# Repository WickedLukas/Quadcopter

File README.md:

# Quadcopter
Teensy 3.6 Quadcopter

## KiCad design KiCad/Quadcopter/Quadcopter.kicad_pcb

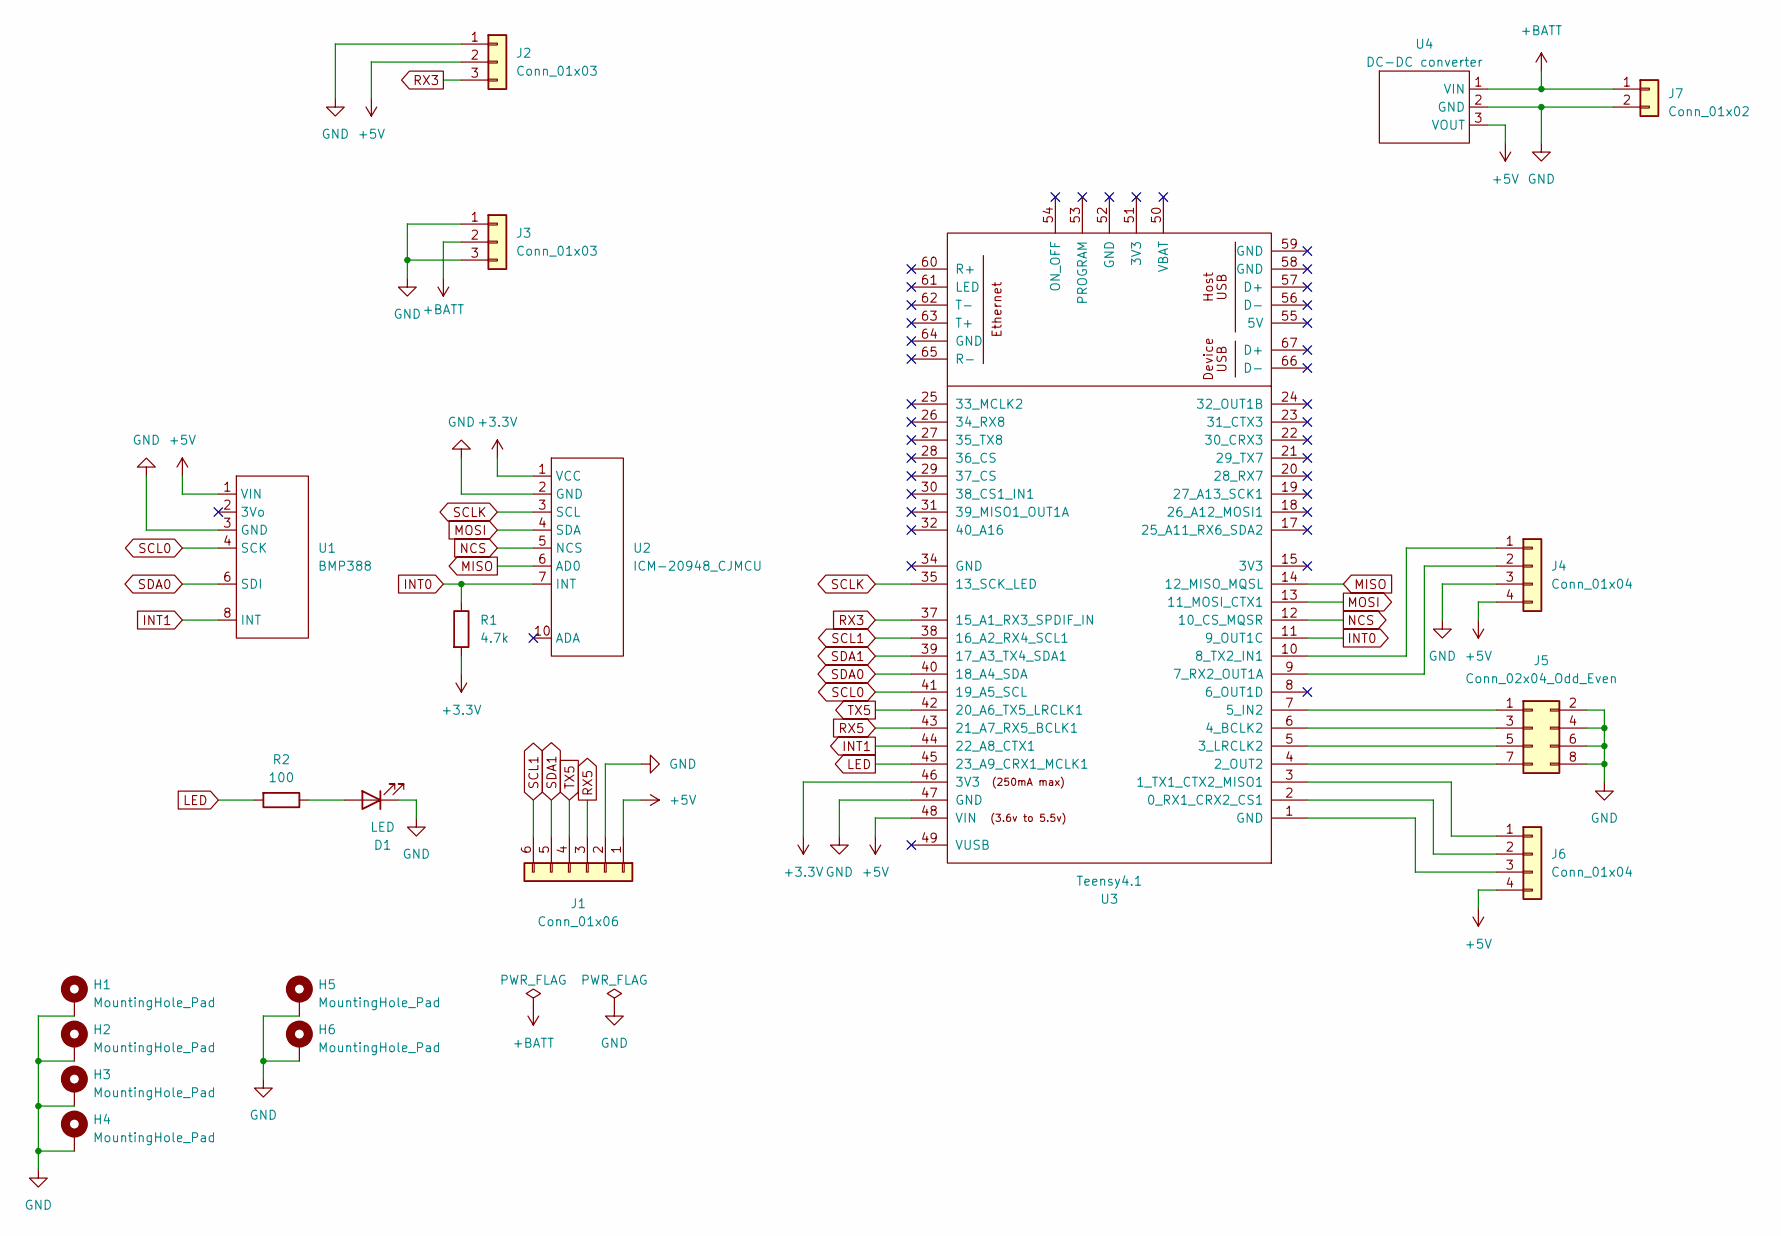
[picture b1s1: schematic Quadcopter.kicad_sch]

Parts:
D1: LED; LED_D5.0mm
H1, H2, H3, H4, H5, H6: MountingHole_Pad; MountingHole_3.2mm_M3_Pad
J1: Conn_01x06; PinHeader_1x06_P2.54mm_Horizontal
J2, J3: Conn_01x03; PinHeader_1x03_P2.54mm_Horizontal
J4, J6: Conn_01x04; PinHeader_1x04_P2.54mm_Horizontal
J5: Conn_02x04_Odd_Even; PinHeader_2x04_P2.54mm_Horizontal
J7: Conn_01x02; 691402910002B
R1: 4.7k; R_Axial_DIN0207_L6.3mm_D2.5mm_P7.62mm_Horizontal
R2: 100; R_Axial_DIN0207_L6.3mm_D2.5mm_P7.62mm_Horizontal
U1: BMP388
U2: ICM-20948_CJMCU
U3: Teensy4.1; Teensy41
U4: DC-DC converter

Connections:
+3.3V: R1.2, U2.1 (VCC), U3.46 (3V3)
+5V: J1.1, J2.2, J4.4, J6.4, U1.1 (VIN), U3.48 (VIN), U4.3 (VOUT)
+BATT: J3.2, J7.1, U4.1 (VIN)
GND: D1.1 (K), H1.1, H2.1, H3.1, H4.1, H5.1, H6.1, J1.2, J2.1, J3.1, J3.3, J4.3, J5.2, J5.4, J5.6, J5.8, J7.2, U1.3 (GND), U2.2 (GND), U3.47 (GND), U4.2 (GND)
INT0: R1.1, U2.7 (INT), U3.11 (9_OUT1C)
INT1: U1.8 (INT), U3.44 (22_A8_CTX1)
LED: R2.2, U3.45 (23_A9_CRX1_MCLK1)
MISO: U2.6 (AD0), U3.14 (12_MISO_MQSL)
MOSI: U2.4 (SDA), U3.13 (11_MOSI_CTX1)
NCS: U2.5 (NCS), U3.12 (10_CS_MQSR)
unnamed: D1.2 (A), R2.1
unnamed: J4.1, U3.10 (8_TX2_IN1)
unnamed: J4.2, U3.9 (7_RX2_OUT1A)
unnamed: J5.1, U3.7 (5_IN2)
unnamed: J5.3, U3.6 (4_BCLK2)
unnamed: J5.5, U3.5 (3_LRCLK2)
unnamed: J5.7, U3.4 (2_OUT2)
unnamed: J6.1, U3.3 (1_TX1_CTX2_MISO1)
unnamed: J6.2, U3.2 (0_RX1_CRX2_CS1)
unnamed: J6.3, U3.1 (GND)
RX3: J2.3, U3.37 (15_A1_RX3_SPDIF_IN)
RX5: J1.3, U3.43 (21_A7_RX5_BCLK1)
SCL0: U1.4 (SCK), U3.41 (19_A5_SCL)
SCL1: J1.6, U3.38 (16_A2_RX4_SCL1)
SCLK: U2.3 (SCL), U3.35 (13_SCK_LED)
SDA0: U1.6 (SDI), U3.40 (18_A4_SDA)
SDA1: J1.5, U3.39 (17_A3_TX4_SDA1)
TX5: J1.4, U3.42 (20_A6_TX5_LRCLK1)

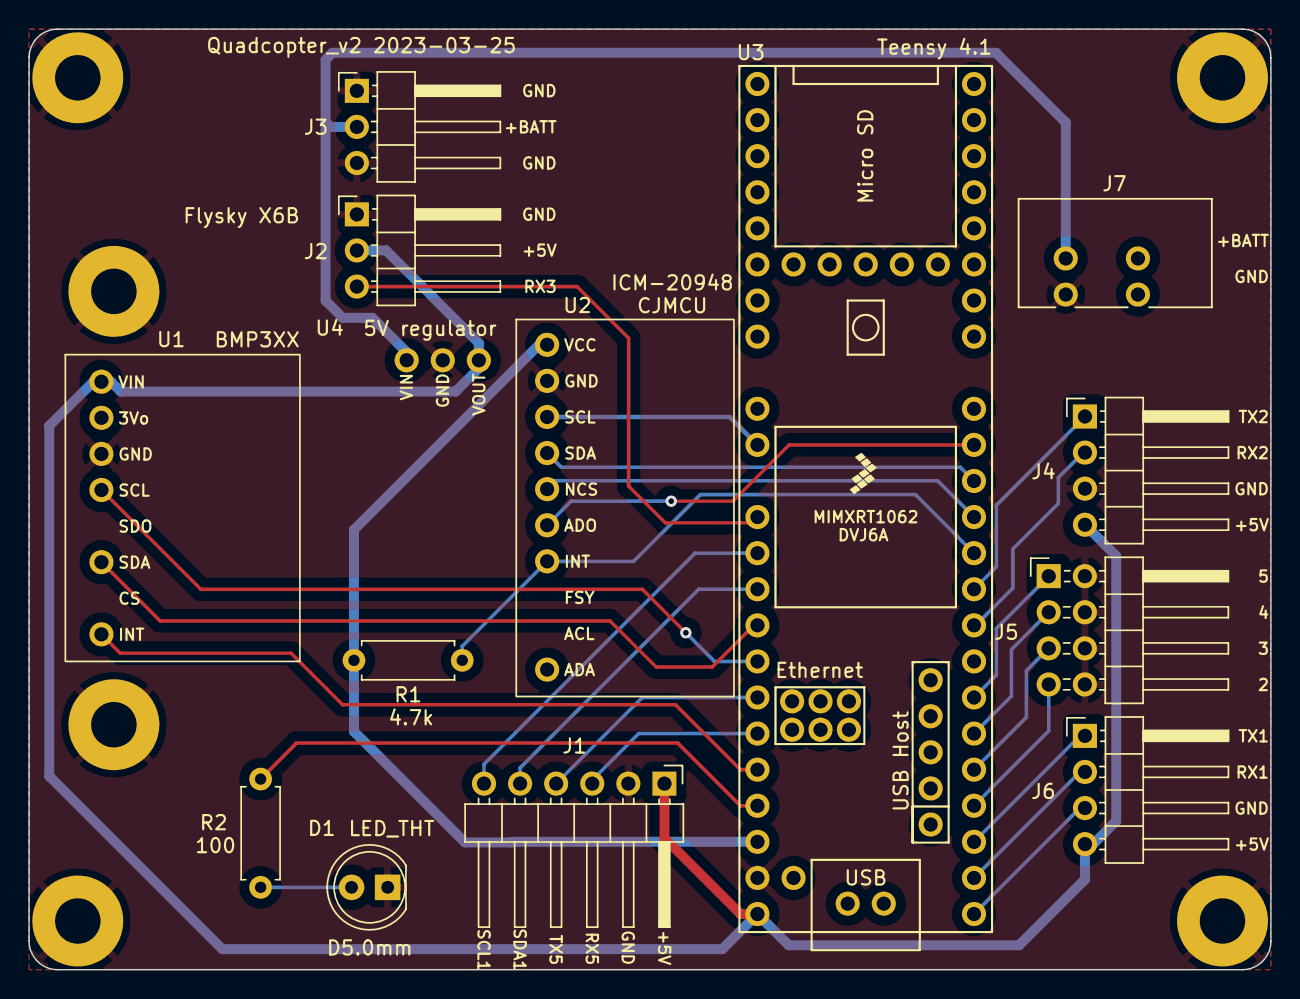
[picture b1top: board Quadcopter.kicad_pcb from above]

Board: 2 copper layers, 87.4 x 66.2 mm, 20 parts (0 on the bottom side), 28 nets.

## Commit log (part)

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2019-04-27 Initial commit which integrates a library for the Invensense ICM-20948 IMU.
    The Invensense ICM-20948 library was created by David Törnqvist and is based on the Invensense MPU-9250 library from Bolder Flight.
2019-05-26 Update to connect to ICM20948 using SPI.
2019-06-10 Read all sensor values at ones.
2019-06-16 Added SPI initialization and fixed a comment.
2019-06-23 Cosmetic changes.
2019-06-30 Included calibration.
2019-07-14 Added MadwickFilter functionality, as well as sendSerial function in order to send results to Processing for visualization.
2019-07-14 Cosmetic change and cleanup.
2019-08-21 Changes for debugging purpose.
2019-08-21 Changed spaces to tabs.
2019-08-22 Reduced unnecessarily big message size inside senSerial.
2019-08-24 Magnetometer hard and soft iron correction is now saved and loaded from eeprom.
2019-09-21 Minor fix.
2019-09-29 Added setpoint calculation by using exponential moving average filters and PID controllers.
2019-10-07 Added DShot ESC protocol and STOP functionality.
2020-02-23 Added TODO comment.
2020-04-05 Removed DShot, since it is way to complicated, does not work for many microcontroller and did not work anyway.
    Updated code to work with Teensy 4.0.
2020-04-05 Added arming procedure.
2020-04-11 Added stable flightmode with tilt compensated thrust.
    Put arming/disarming procedure into separate function.
2020-04-14 Preperations for failsafe implementation (restructuring).
    Preparation for status indication via LED.
2020-04-15 Fixed a bug that pid controller was working on the yaw angle instead of the angular velocity.
    Added failsafe features.
2020-04-15 Introduced status LED.
2020-04-16 Motors will run immediately when armed, but PID calculations will still be delayed until a minimum throttle is reached in order to ensure a smooth start.
2020-04-16 Minot optimizations.
2020-04-16 Important bugfixes and optimizations!
2020-04-16 Fixed a bug that imu failsafe was not working.
2020-04-17 Minor cleanup and optimization.
2020-04-19 Fixed a bug in LED control.
2020-04-25 Removed ema filter from gyro rates.
2020-04-26 Renamed some variables, bugfixes in PID controller and PID controller tuning.
2020-05-01 cleanup
2020-08-08 Some parameter optimizations and renaming.
2020-08-08 Fixed wrong PID limit.
2020-08-09 - Parameter optimizations. - Fixed a bug in pitch rate controller parameter. - Fixed a bug when arming again.
2020-08-13 Added functionality of saving and loading gyroscope and accelerometer calibration data as well as some optimizations.
2020-08-14 - Hover throttle can now be centered to the middle stick position. - Increased maximum roll and pitch acceleration. - Improvements for stable flight mode with tilt compensated thrust. - Motors will s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
2020-08-16 Cleaned up comment.
2020-08-19 Updated comments.
2020-08-23 - Changed tilt compensated thrust calculation to using quaternions, because it is computationally more efficient. - wip: altitude calculation - calculate acceleration in ned-frame.
2020-08-23 Implemented altitude estimation from pose, accelerometer and barometric pressure sensor.
2020-08-28 Bugfix for yaw_rate and some renaming, because existing functions can be used for altitude hold.
    wip: altitude hold
2020-09-06 Minor optimization and cleanup.
2020-09-06 - Major bugfix in yaw control. - Yaw PI controller can be tuned using remote.
2020-09-14 Introduced THROTTLE_ARM and THROTTLE_MIN. Changed the range for yaw PID tuning.
2020-09-15 Major refractoring for motor control.
2020-09-15 Cosmetic change.
2020-09-17 Updated wind-up compensation and limits for PID controller.
2020-09-19 Parameter optimizations.
2020-09-19 - Increased failsafe limit (yaw rate). - Parameter optimizations.
2021-02-21 - Minor bugfix for new barometer library. - Updated gitignore.
2021-03-06 Fixed that rates were not calculated.
2021-03-28 Add EMA filtering for rates.
2021-03-28 Separate filtering for proportional controller!
2021-03-28 Optimizations for PID tuning.
2021-03-29 Fixed a major problem that too much data was plotted which finally resulted in an unstable flight!
2021-03-29 Optimizations for filtering parameters
2021-04-01 Some parameter optimizations.
2021-04-02 Major parameter optimizations, especially for yaw rate PID.
2021-04-04 Major changes: - Add throttle expo to achieve less throttle sensitivity around hover. - Significant changes to altitude hold PID and filtering. - Use tilt compensated thrust in altitude hold mode. - 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
2021-04-04 - Minor bugfix in plotting and minor parameter optimizations for altitude hold.
2021-04-10 Added TODOs and updated some comments.
2021-04-17 Major rework for altitude hold. - rework altitude hold mode to control vertical velocity - remove TROTTLE_MIN parameter for a more linear throttle experience - increase THROTTLE_ARMED - refactoring f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
2022-05-27 PIO changes.
2022-05-28 Major refactoring.
2022-06-05 - Make it optional which sensors to use (magnetometer, barometer, gps). - Make some global variables static to limit scope to a file. - Add NeoGPS library from SlashDevin (wip). - Give serial ports s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
2022-06-06 - major cleanup. - introduce define to disable motors for safety
2022-06-06 - Minor optimization for initial yaw angle and initial altitude. - Rename functions used for initialisation.
2022-06-06 Add lib-folder including subdirectories to .gitignore.
2022-06-11 - Calculate distance from launch using gps. - Reset altitude and distance from launch filter when disarming.
2022-06-11 Bugfix with variable names and some wrong variable name in debug message.
2022-06-11 Fix bug with distance from launch update.
2022-06-12 Change yaw range from [-180, 180] to [0, 360] in order to match gps heading and bearing.
2022-06-12 Fix distance from launch updating.
2022-06-18 Adjust yaw angle to match with gps heading.
2022-06-19 Rename some files.
2022-06-19 - Introduce return to launch (RTL) functionality (untested).
2022-06-19 Fix bug from in last commit.
2022-06-19 - Clean up calibration interface using arrays. - Initialization now resets everything.
2022-06-25 Make the quadcopter face the launch location only when actually returning to launch and not while climbing or descending.
2022-06-25 Important bugfix for throttle.
2022-06-26 Replace if / else with switch / case statement. No functional change.
2022-07-24 Fix bug when limiting yaw angle range.
2022-07-24 Adjust range for manual PID tuning.
2022-08-26 Use tilt compensated thrust for AltitudeHold and ReturnToLaunch.
2022-08-29 - Reworked Return To Launch (RTL). - Disable yaw angle correction in RTL mode, because it is not working yet. - Lowered requirement for solid GPS fix. - Increase maximum yaw rate and tilt angle.
2022-08-30 - fix position and velocity orientation - fix that north and east velocity were not determined - reduce satellite requirement for a solid gps fix - pid tuning for vertical velocity controller - param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
2022-09-01 - Major rework for return to launch. Distances in ned and horizontal coordinates are now correctly calculated (correct sign) using bearing and distance. - optimize vertical velocity controller pid - 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
2022-09-07 - constrain yaw rate during RTL - update some parameters according to arducopter
2022-09-08 remove unnecessary file
2022-09-24 Fix major bugs in RTL mode and parameter optimizations.
2022-09-25 - Replace IMU acceleration filtering with stronger EMA acceleration filtering for more robust angle estimation in noisy environment. - Some parameter optimizations.
2022-09-30 Fix compatibility with new PID_controller library.
2022-10-01 Configuration for vscode.
2022-10-03 PID optimizations.
2022-10-03 Minor fix for last commit.
2022-10-05 fix: Fix yaw angle rotation direction during RTL.
2022-10-05 PID optimizations
2023-03-23 Add KiCad PCB files.
2023-03-25 Remove obsolete files.
2023-04-02 refactor: navigation code
2023-04-10 Minor refactoring
    - move some code into functions
2023-04-10 Fix compilation error with different sensor setup
2023-04-16 Basic integration of sd card logging.
    - make log interval configurable
    - do not return an error when SD card is missing
2023-04-16 Change data logger log function to templates for better performance and flexibility
2023-04-16 Major optimizations for data logger
    - the line to log does not need to fit into the sector size cache anymore
    - the line to log can now be written to the SD card during the whole log interval
    - increase ring buffer size
2023-04-16 Configure SD card logging
    - Add some helper macros for SD card logging.
2023-04-17 Add sample and time to data log.
2023-04-17 Calculate the used ring buffer correctly.
2023-04-23 Change IDE settings to Teensy 4.1
2023-04-28 Fix enabling and disabling sd card logging.
2023-04-29 Get SD card logging running.
2023-04-29 Minor optimization for sd card log timing.
2023-04-30 Increase accuracy for SD card logging.
2023-04-30 Update gitignore file and remove KiCad cache file from repository.
2023-04-30 Add some debug logs.
2023-04-30 Workaround for inconsistencies in update time and fix false GPS error
2023-04-30 Update TelemetryViewer config missing in last commit.
2023-05-01 Minor optimizations for SD card logger.
    - increase maximum log file size and calculate maximum number of log files
    - remove some unnecessary code
    - slightly modify log file names
2023-05-02 Add PID controller terms to SD card logger.
2023-05-06 Optimise parameters for roll/pitch rate PID controller.
2023-05-06 Lower acceleration limit for roll and pitch.
2023-05-07 Remove throttle expo and adjust throttle limits
    - we want a linear thrust curve and throttle expo makes it worse for high throttle
    - increase minimum throttle and throttle hover
2023-08-19 Increase accuracy for data logger.
2023-08-22 Use correct gps serial port for new hardware (PCB).
2023-08-25 Minor refactoring - remove parameter MOTOR_PWM_RESOLUTION
2023-08-25 Add .bak files to .gitignore
2023-08-26 Fix comment.
2023-08-26 PID optimisations - for linearised thrust response - for more robustness against vibrations
2023-08-27 Minor update for TelemetryViewer layout.
2023-08-28 Increase precision for altitude for a more accurate vertical velocity.
2023-08-30 Refactor filtering - filter measurements (mainly for SD card logging) separately with the same filter like the one used for the P-term of the matching PID controller.
2023-08-31 Use filtered yaw rate for motion failsafe.
2023-08-31 Calculate vertical velocity based on filtered altitude.
2023-08-31 Minor cleanup.
2023-09-01 Add TelemetryViewer configuration.
2023-09-02 Enter started state with active PID controller with less than hover throttle to make sure self balancing works on take off.
2023-09-04 Major parameter optimisations
    - stabilisation
    - altitude hold
    - RTL
2023-09-05 Change RTL behaviour
2023-09-07 Fix bug in heading correction calculation (currently disabled)
    - fix bearing calculation necessary for heading calculation
    - round motor output properly
    - remove obsolete accelRes variable
2023-09-23 Use a fix RTL altitude and a minimum RTL altitude.
2023-12-01 Fix bug for RTL.
2023-12-01 Remove commented out code from WpNav class
